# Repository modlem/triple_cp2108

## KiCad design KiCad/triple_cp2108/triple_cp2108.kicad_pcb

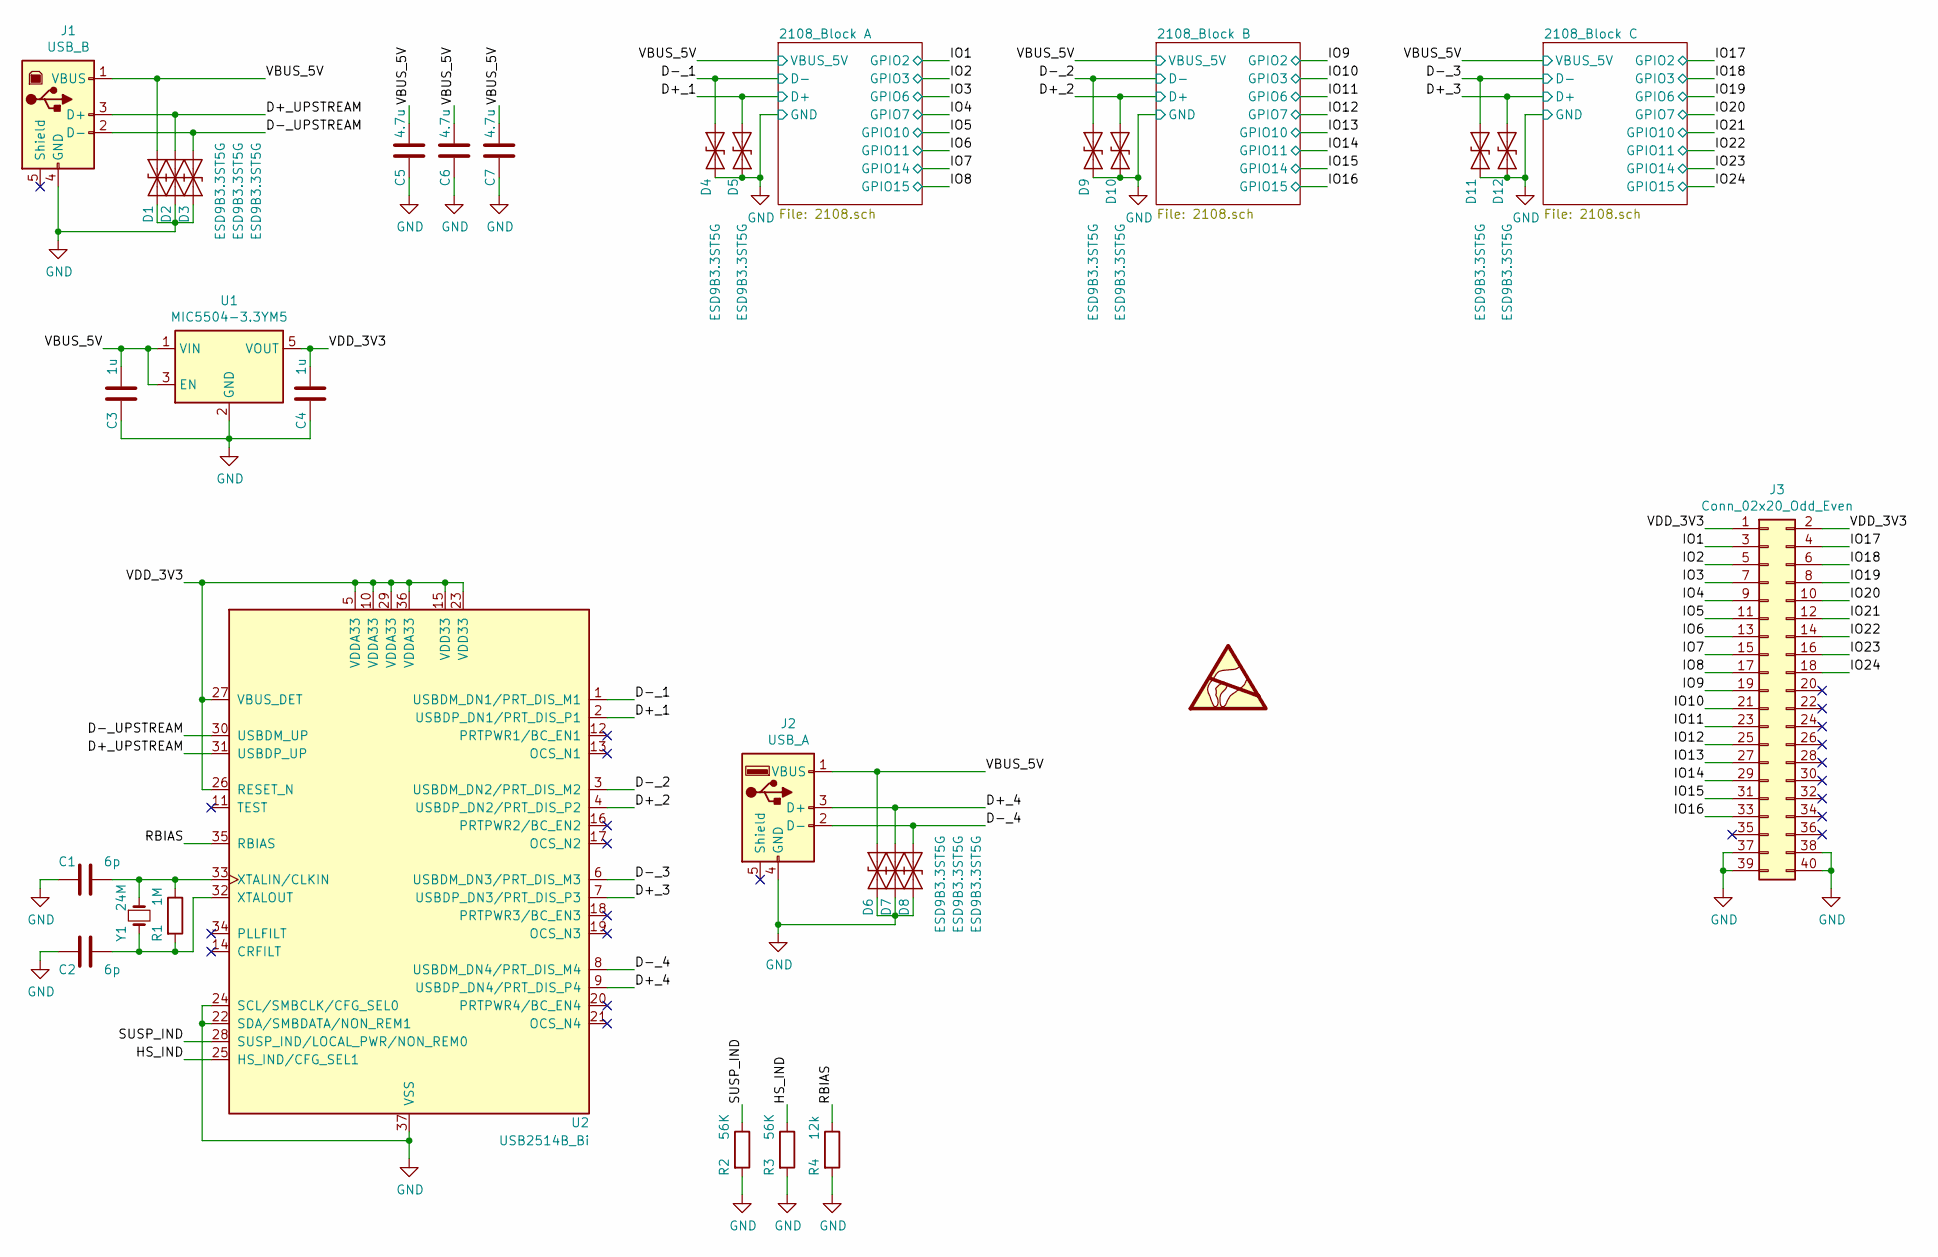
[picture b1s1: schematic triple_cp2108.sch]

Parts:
C1, C2: 6p; C_0805_2012Metric_Pad1.18x1.45mm_HandSolder
C3, C4: 1u; C_0805_2012Metric_Pad1.18x1.45mm_HandSolder
C5, C6, C7: 4.7u; C_0805_2012Metric_Pad1.18x1.45mm_HandSolder
D1, D2, D3, D4, D5, D6, D7, D8, D9, D10, D11, D12: ESD9B3.3ST5G; D_SOD-923
J1: USB_B; USB_B_OST_USB-B1HSxx_Horizontal
J2: USB_A; USB_A_CONNFLY_DS1095-WNR0
J3: Conn_02x20_Odd_Even; PinHeader_2x20_P2.54mm_Vertical
R1: 1M; R_0805_2012Metric_Pad1.20x1.40mm_HandSolder
R2, R3: 56K; R_0805_2012Metric_Pad1.20x1.40mm_HandSolder
R4: 12k; R_0805_2012Metric_Pad1.20x1.40mm_HandSolder
U1: MIC5504-3.3YM5; SOT-23-5
U2: USB2514B_Bi; QFN-36-1EP_6x6mm_P0.5mm_EP3.7x3.7mm
Y1: 24M; Crystal_SMD_2016-4Pin_2.0x1.6mm; Manufacturer_Part_Number XRCGB24M000F2P00R0

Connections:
/D+_1: D5.1 (A1), U2.2 (USBDP_DN1/PRT_DIS_P1); also elsewhere on the board
/D+_2: D10.1 (A1), U2.4 (USBDP_DN2/PRT_DIS_P2); also elsewhere on the board
/D+_3: D12.1 (A1), U2.7 (USBDP_DN3/PRT_DIS_P3); also elsewhere on the board
/D+_4: D7.1 (A1), J2.3 (D+), U2.9 (USBDP_DN4/PRT_DIS_P4)
/D+_UPSTREAM: D2.1 (A1), J1.3 (D+), U2.31 (USBDP_UP)
/D-_1: D4.1 (A1), U2.1 (USBDM_DN1/PRT_DIS_M1); also elsewhere on the board
/D-_2: D9.1 (A1), U2.3 (USBDM_DN2/PRT_DIS_M2); also elsewhere on the board
/D-_3: D11.1 (A1), U2.6 (USBDM_DN3/PRT_DIS_M3); also elsewhere on the board
/D-_4: D8.1 (A1), J2.2 (D-), U2.8 (USBDM_DN4/PRT_DIS_M4)
/D-_UPSTREAM: D3.1 (A1), J1.2 (D-), U2.30 (USBDM_UP)
/HS_IND: R3.1, U2.25 (HS_IND/CFG_SEL1)
/IO1: J3.3; also elsewhere on the board
/IO2: J3.5; also elsewhere on the board
/IO3: J3.7; also elsewhere on the board
/IO4: J3.9; also elsewhere on the board
/IO5: J3.11; also elsewhere on the board
/IO6: J3.13; also elsewhere on the board
/IO7: J3.15; also elsewhere on the board
/IO8: J3.17; also elsewhere on the board
/IO9: J3.19; also elsewhere on the board
/IO10: J3.21; also elsewhere on the board
/IO11: J3.23; also elsewhere on the board
/IO12: J3.25; also elsewhere on the board
/IO13: J3.27; also elsewhere on the board
/IO14: J3.29; also elsewhere on the board
/IO15: J3.31; also elsewhere on the board
/IO16: J3.33; also elsewhere on the board
/IO17: J3.4; also elsewhere on the board
/IO18: J3.6; also elsewhere on the board
/IO19: J3.8; also elsewhere on the board
/IO20: J3.10; also elsewhere on the board
/IO21: J3.12; also elsewhere on the board
/IO22: J3.14; also elsewhere on the board
/IO23: J3.16; also elsewhere on the board
/IO24: J3.18; also elsewhere on the board
/RBIAS: R4.1, U2.35 (RBIAS)
/SUSP_IND: R2.1, U2.28 (SUSP_IND/LOCAL_PWR/NON_REM0)
/VBUS_5V: C3.2, C5.2, C6.2, C7.2, D1.1 (A1), D6.1 (A1), J1.1 (VBUS), J2.1 (VBUS), U1.1 (VIN), U1.3 (EN); also elsewhere on the board
/VDD_3V3: C4.2, J3.1, J3.2, U1.5 (VOUT), U2.5 (VDDA33), U2.10 (VDDA33), U2.15 (VDD33), U2.23 (VDD33), U2.26 (RESET_N), U2.27 (VBUS_DET), U2.29 (VDDA33), U2.36 (VDDA33)
GND: C1.2, C2.2, C3.1, C4.1, C5.1, C6.1, C7.1, D1.2 (A2), D2.2 (A2), D3.2 (A2), D4.2 (A2), D5.2 (A2), D6.2 (A2), D7.2 (A2), D8.2 (A2), D9.2 (A2), D10.2 (A2), D11.2 (A2), D12.2 (A2), J1.4 (GND), J2.4 (GND), J3.37, J3.38, J3.39, J3.40, R2.2, R3.2, R4.2, U1.2 (GND), U2.22 (SDA/SMBDATA/NON_REM1), U2.24 (SCL/SMBCLK/CFG_SEL0), U2.37 (VSS); also elsewhere on the board
unnamed: C1.1, R1.1, U2.33 (XTALIN/CLKIN), Y1.1
unnamed: C2.1, R1.2, U2.32 (XTALOUT), Y1.2

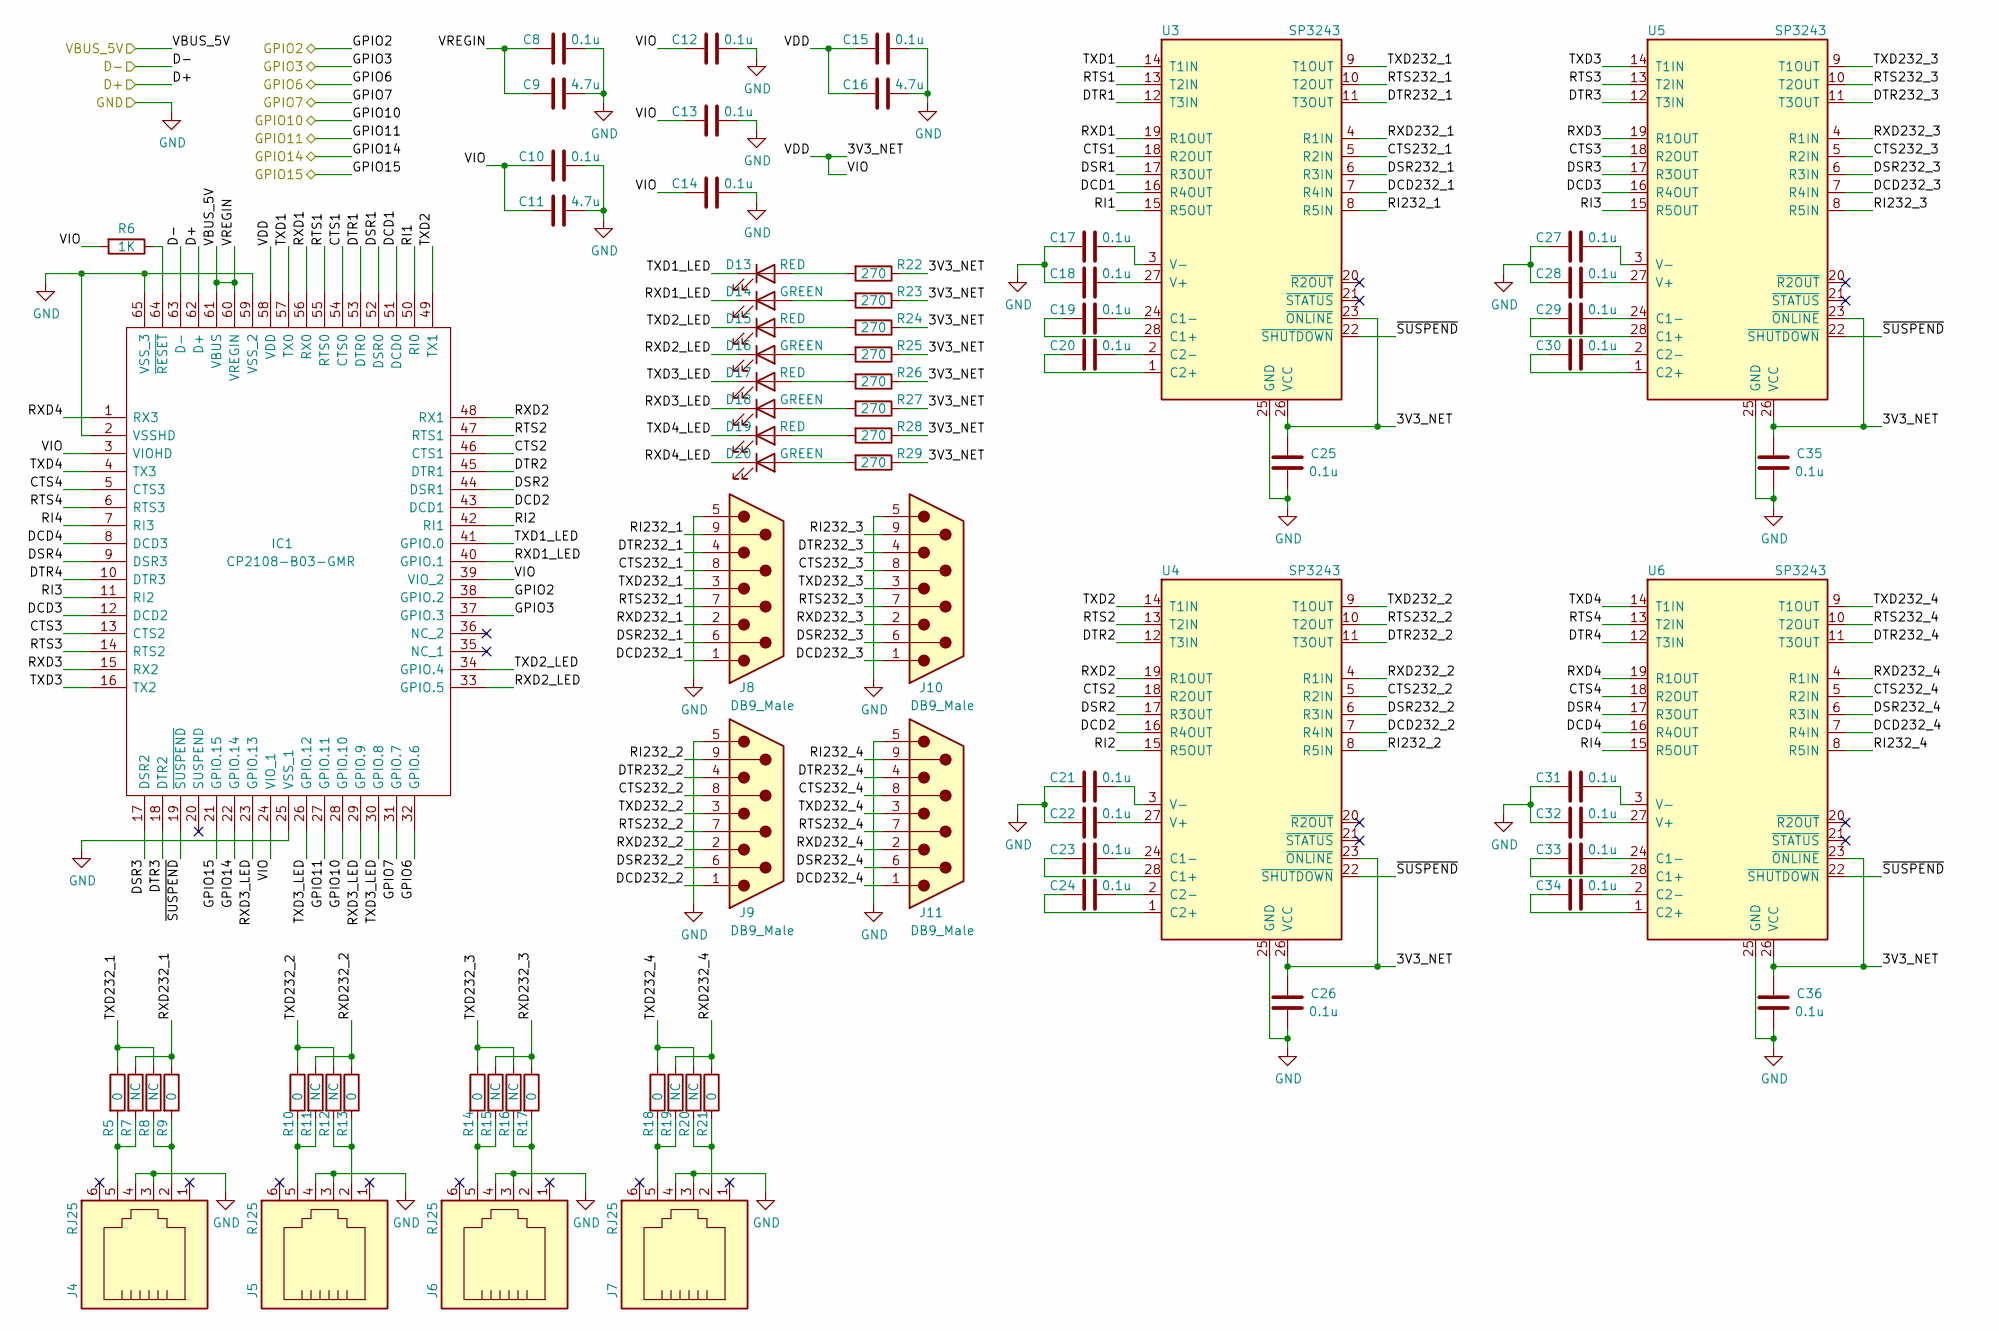
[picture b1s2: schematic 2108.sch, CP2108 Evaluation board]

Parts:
C8, C10, C12, C13, C14, C15, C17, C18, C19, C20, C21, C22, C23, C24, C25, C26, C27, C28, C29, C30, C31, C32, C33, C34, C35, C36: 0.1u; C_0805_2012Metric_Pad1.18x1.45mm_HandSolder; Manufacturer_Part_Number C0805C104M5RACTU
C9, C11, C16: 4.7u; C_0805_2012Metric_Pad1.18x1.45mm_HandSolder
D13, D15, D17, D19: RED; LED_0603_1608Metric; Manufacturer_Part_Number LTST-C193KRKT-5A
D14, D16, D18, D20: GREEN; LED_0603_1608Metric; Manufacturer_Part_Number LTST-C193KGKT-5A
IC1: CP2108-B03-GMR; QFN50P900X900X90-65N-D; Mouser Part Number 634-CP2108-B03-GMR
J4, J5, J6, J7: RJ25; RJ25_Wayconn_MJEA-660X1_Horizontal
J8, J9, J10, J11: DB9_Male; DSUB-9_Male_Vertical_P2.77x2.84mm
R5, R9, R10, R13, R14, R17, R18, R21: 0; R_0805_2012Metric_Pad1.20x1.40mm_HandSolder
R6: 1K; R_0805_2012Metric_Pad1.20x1.40mm_HandSolder
R7, R8, R11, R12, R15, R16, R19, R20: NC; R_0805_2012Metric_Pad1.20x1.40mm_HandSolder
R22, R23, R24, R25, R26, R27, R28, R29: 270; R_0805_2012Metric_Pad1.20x1.40mm_HandSolder
U3, U4, U5, U6: SP3243; SSOP-28_5.3x10.2mm_P0.65mm; Manufacturer_Part_Number SP3243EUEY-L/TR

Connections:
/2108_Block A/3V3_NET: C10.2, C11.2, C12.2, C13.2, C14.2, C15.2, C16.2, C25.2, C26.2, C35.2, C36.2, IC1.3 (VIOHD), IC1.24 (VIO_1), IC1.39 (VIO_2), IC1.58 (VDD), R6.2, R22.1, R23.1, R24.1, R25.1, R26.1, R27.1, R28.1, R29.1, U3.23 (~ONLINE), U3.26 (VCC), U4.23 (~ONLINE), U4.26 (VCC), U5.23 (~ONLINE), U5.26 (VCC), U6.23 (~ONLINE), U6.26 (VCC)
/2108_Block A/CTS1: IC1.54 (CTS0), U3.18 (R2OUT)
/2108_Block A/CTS2: IC1.46 (CTS1), U4.18 (R2OUT)
/2108_Block A/CTS3: IC1.13 (CTS2), U5.18 (R2OUT)
/2108_Block A/CTS4: IC1.5 (CTS3), U6.18 (R2OUT)
/2108_Block A/CTS232_1: J8.8, U3.5 (R2IN)
/2108_Block A/CTS232_2: J9.8, U4.5 (R2IN)
/2108_Block A/CTS232_3: J10.8, U5.5 (R2IN)
/2108_Block A/CTS232_4: J11.8, U6.5 (R2IN)
/2108_Block A/DCD1: IC1.51 (DCD0), U3.16 (R4OUT)
/2108_Block A/DCD2: IC1.43 (DCD1), U4.16 (R4OUT)
/2108_Block A/DCD3: IC1.12 (DCD2), U5.16 (R4OUT)
/2108_Block A/DCD4: IC1.8 (DCD3), U6.16 (R4OUT)
/2108_Block A/DCD232_1: J8.1, U3.7 (R4IN)
/2108_Block A/DCD232_2: J9.1, U4.7 (R4IN)
/2108_Block A/DCD232_3: J10.1, U5.7 (R4IN)
/2108_Block A/DCD232_4: J11.1, U6.7 (R4IN)
/2108_Block A/DSR1: IC1.52 (DSR0), U3.17 (R3OUT)
/2108_Block A/DSR2: IC1.44 (DSR1), U4.17 (R3OUT)
/2108_Block A/DSR3: IC1.17 (DSR2), U5.17 (R3OUT)
/2108_Block A/DSR4: IC1.9 (DSR3), U6.17 (R3OUT)
/2108_Block A/DSR232_1: J8.6, U3.6 (R3IN)
/2108_Block A/DSR232_2: J9.6, U4.6 (R3IN)
/2108_Block A/DSR232_3: J10.6, U5.6 (R3IN)
/2108_Block A/DSR232_4: J11.6, U6.6 (R3IN)
/2108_Block A/DTR1: IC1.53 (DTR0), U3.12 (T3IN)
/2108_Block A/DTR2: IC1.45 (DTR1), U4.12 (T3IN)
/2108_Block A/DTR3: IC1.18 (DTR2), U5.12 (T3IN)
/2108_Block A/DTR4: IC1.10 (DTR3), U6.12 (T3IN)
/2108_Block A/DTR232_1: J8.4, U3.11 (T3OUT)
/2108_Block A/DTR232_2: J9.4, U4.11 (T3OUT)
/2108_Block A/DTR232_3: J10.4, U5.11 (T3OUT)
/2108_Block A/DTR232_4: J11.4, U6.11 (T3OUT)
/2108_Block A/RI1: IC1.50 (RI0), U3.15 (R5OUT)
/2108_Block A/RI2: IC1.42 (RI1), U4.15 (R5OUT)
/2108_Block A/RI3: IC1.11 (RI2), U5.15 (R5OUT)
/2108_Block A/RI4: IC1.7 (RI3), U6.15 (R5OUT)
/2108_Block A/RI232_1: J8.9, U3.8 (R5IN)
/2108_Block A/RI232_2: J9.9, U4.8 (R5IN)
/2108_Block A/RI232_3: J10.9, U5.8 (R5IN)
/2108_Block A/RI232_4: J11.9, U6.8 (R5IN)
/2108_Block A/RTS1: IC1.55 (RTS0), U3.13 (T2IN)
/2108_Block A/RTS2: IC1.47 (RTS1), U4.13 (T2IN)
/2108_Block A/RTS3: IC1.14 (RTS2), U5.13 (T2IN)
/2108_Block A/RTS4: IC1.6 (RTS3), U6.13 (T2IN)
/2108_Block A/RTS232_1: J8.7, U3.10 (T2OUT)
/2108_Block A/RTS232_2: J9.7, U4.10 (T2OUT)
/2108_Block A/RTS232_3: J10.7, U5.10 (T2OUT)
/2108_Block A/RTS232_4: J11.7, U6.10 (T2OUT)
/2108_Block A/RXD1: IC1.56 (RX0), U3.19 (R1OUT)
/2108_Block A/RXD1_LED: D14.1 (K), IC1.40 (GPIO.1)
/2108_Block A/RXD2: IC1.48 (RX1), U4.19 (R1OUT)
/2108_Block A/RXD2_LED: D16.1 (K), IC1.33 (GPIO.5)
/2108_Block A/RXD3: IC1.15 (RX2), U5.19 (R1OUT)
/2108_Block A/RXD4: IC1.1 (RX3), U6.19 (R1OUT)
/2108_Block A/RXD232_1: J8.2, R7.1, R9.1, U3.4 (R1IN)
/2108_Block A/RXD232_2: J9.2, R11.1, R13.1, U4.4 (R1IN)
/2108_Block A/RXD232_3: J10.2, R15.1, R17.1, U5.4 (R1IN)
/2108_Block A/RXD232_4: J11.2, R19.1, R21.1, U6.4 (R1IN)
/2108_Block A/TXD1: IC1.57 (TX0), U3.14 (T1IN)
/2108_Block A/TXD1_LED: D13.1 (K), IC1.41 (GPIO.0)
/2108_Block A/TXD2: IC1.49 (TX1), U4.14 (T1IN)
/2108_Block A/TXD2_LED: D15.1 (K), IC1.34 (GPIO.4)
/2108_Block A/TXD3: IC1.16 (TX2), U5.14 (T1IN)
/2108_Block A/TXD4: IC1.4 (TX3), U6.14 (T1IN)
/2108_Block A/TXD232_1: J8.3, R5.1, R8.1, U3.9 (T1OUT)
/2108_Block A/TXD232_2: J9.3, R10.1, R12.1, U4.9 (T1OUT)
/2108_Block A/TXD232_3: J10.3, R14.1, R16.1, U5.9 (T1OUT)
/2108_Block A/TXD232_4: J11.3, R18.1, R20.1, U6.9 (T1OUT)
/2108_Block A/~SUSPEND: IC1.19 (~SUSPEND), U3.22 (~SHUTDOWN), U4.22 (~SHUTDOWN), U5.22 (~SHUTDOWN), U6.22 (~SHUTDOWN)
/D+_1: IC1.62 (D+); also elsewhere on the board
/D-_1: IC1.63 (D-); also elsewhere on the board
/IO1: IC1.38 (GPIO.2); also elsewhere on the board
/IO2: IC1.37 (GPIO.3); also elsewhere on the board
/IO3: IC1.32 (GPIO.6); also elsewhere on the board
/IO4: IC1.31 (GPIO.7); also elsewhere on the board
/IO5: IC1.28 (GPIO.10); also elsewhere on the board
/IO6: IC1.27 (GPIO.11); also elsewhere on the board
/IO7: IC1.22 (GPIO.14); also elsewhere on the board
/IO8: IC1.21 (GPIO.15); also elsewhere on the board
/VBUS_5V: C8.2, C9.2, IC1.60 (VREGIN), IC1.61 (VBUS); also elsewhere on the board
GND: C8.1, C9.1, C10.1, C11.1, C12.1, C13.1, C14.1, C15.1, C16.1, C17.2, C18.2, C21.2, C22.2, C25.1, C26.1, C27.2, C28.2, C31.2, C32.2, C35.1, C36.1, IC1.2 (VSSHD), IC1.25 (VSS_1), IC1.59 (VSS_2), IC1.65 (VSS_3), J4.3, J4.4, J5.3, J5.4, J6.3, J6.4, J7.3, J7.4, J8.5, J9.5, J10.5, J11.5, U3.25 (GND), U4.25 (GND), U5.25 (GND), U6.25 (GND); also elsewhere on the board
unnamed: C17.1, U3.3 (V-)
unnamed: C18.1, U3.27 (V+)
unnamed: C19.1, U3.24 (C1-)
unnamed: C19.2, U3.28 (C1+)
unnamed: C20.1, U3.2 (C2-)
unnamed: C20.2, U3.1 (C2+)
unnamed: C21.1, U4.3 (V-)
unnamed: C22.1, U4.27 (V+)
unnamed: C23.1, U4.24 (C1-)
unnamed: C23.2, U4.28 (C1+)
unnamed: C24.1, U4.2 (C2-)
unnamed: C24.2, U4.1 (C2+)
unnamed: C27.1, U5.3 (V-)
unnamed: C28.1, U5.27 (V+)
unnamed: C29.1, U5.24 (C1-)
unnamed: C29.2, U5.28 (C1+)
unnamed: C30.1, U5.2 (C2-)
unnamed: C30.2, U5.1 (C2+)
unnamed: C31.1, U6.3 (V-)
unnamed: C32.1, U6.27 (V+)
unnamed: C33.1, U6.24 (C1-)
unnamed: C33.2, U6.28 (C1+)
unnamed: C34.1, U6.2 (C2-)
unnamed: C34.2, U6.1 (C2+)
unnamed: D13.2 (A), R22.2
unnamed: D14.2 (A), R23.2
unnamed: D15.2 (A), R24.2
unnamed: D16.2 (A), R25.2
unnamed: D17.2 (A), R26.2
unnamed: D18.2 (A), R27.2
unnamed: D19.2 (A), R28.2
unnamed: D20.2 (A), R29.2
unnamed: IC1.64 (~RESET), R6.1
unnamed: J4.2, R8.2, R9.2
unnamed: J4.5, R5.2, R7.2
unnamed: J5.2, R12.2, R13.2
unnamed: J5.5, R10.2, R11.2
unnamed: J6.2, R16.2, R17.2
unnamed: J6.5, R14.2, R15.2
unnamed: J7.2, R20.2, R21.2
unnamed: J7.5, R18.2, R19.2

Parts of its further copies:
C37, C39, C41, C42, C43, C44, C46, C47, C48, C49, C50, C51, C52, C53, C54, C55, C56, C57, C58, C59, C60, C61, C62, C63, C64, C65, C66, C68, C70, C71, C72, C73, C75, C76, C77, C78, C79, C80, C81, C82, C83, C84, C85, C86, C87, C88, C89, C90, C91, C92, C93, C94: 0.1u; C_0805_2012Metric_Pad1.18x1.45mm_HandSolder; Manufacturer_Part_Number C0805C104M5RACTU
C38, C40, C45, C67, C69, C74: 4.7u; C_0805_2012Metric_Pad1.18x1.45mm_HandSolder
D21, D23, D25, D27, D29, D31, D33, D35: RED; LED_0603_1608Metric; Manufacturer_Part_Number LTST-C193KRKT-5A
D22, D24, D26, D28, D30, D32, D34, D36: GREEN; LED_0603_1608Metric; Manufacturer_Part_Number LTST-C193KGKT-5A
IC2, IC3: CP2108-B03-GMR; QFN50P900X900X90-65N-D; Mouser Part Number 634-CP2108-B03-GMR
J12, J13, J14, J15, J20, J21, J22, J23: RJ25; RJ25_Wayconn_MJEA-660X1_Horizontal
J16, J17, J18, J19, J24, J25, J26, J27: DB9_Male; DSUB-9_Male_Vertical_P2.77x2.84mm
R30, R34, R35, R38, R39, R42, R43, R46, R55, R59, R60, R63, R64, R67, R68, R71: 0; R_0805_2012Metric_Pad1.20x1.40mm_HandSolder
R31, R56: 1K; R_0805_2012Metric_Pad1.20x1.40mm_HandSolder
R32, R33, R36, R37, R40, R41, R44, R45, R57, R58, R61, R62, R65, R66, R69, R70: NC; R_0805_2012Metric_Pad1.20x1.40mm_HandSolder
R47, R48, R49, R50, R51, R52, R53, R54, R72, R73, R74, R75, R76, R77, R78, R79: 270; R_0805_2012Metric_Pad1.20x1.40mm_HandSolder
U7, U8, U9, U10, U11, U12, U13, U14: SP3243; SSOP-28_5.3x10.2mm_P0.65mm; Manufacturer_Part_Number SP3243EUEY-L/TR

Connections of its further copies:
/2108_Block B/3V3_NET: C39.2, C40.2, C41.2, C42.2, C43.2, C44.2, C45.2, C54.2, C55.2, C64.2, C65.2, IC2.3 (VIOHD), IC2.24 (VIO_1), IC2.39 (VIO_2), IC2.58 (VDD), R31.2, R47.1, R48.1, R49.1, R50.1, R51.1, R52.1, R53.1, R54.1, U7.23 (~ONLINE), U7.26 (VCC), U8.23 (~ONLINE), U8.26 (VCC), U9.23 (~ONLINE), U9.26 (VCC), U10.23 (~ONLINE), U10.26 (VCC)
/2108_Block B/CTS1: IC2.54 (CTS0), U7.18 (R2OUT)
/2108_Block B/CTS2: IC2.46 (CTS1), U8.18 (R2OUT)
/2108_Block B/CTS3: IC2.13 (CTS2), U9.18 (R2OUT)
/2108_Block B/CTS4: IC2.5 (CTS3), U10.18 (R2OUT)
/2108_Block B/CTS232_1: J16.8, U7.5 (R2IN)
/2108_Block B/CTS232_2: J17.8, U8.5 (R2IN)
/2108_Block B/CTS232_3: J18.8, U9.5 (R2IN)
/2108_Block B/CTS232_4: J19.8, U10.5 (R2IN)
/2108_Block B/DCD1: IC2.51 (DCD0), U7.16 (R4OUT)
/2108_Block B/DCD2: IC2.43 (DCD1), U8.16 (R4OUT)
/2108_Block B/DCD3: IC2.12 (DCD2), U9.16 (R4OUT)
/2108_Block B/DCD4: IC2.8 (DCD3), U10.16 (R4OUT)
/2108_Block B/DCD232_1: J16.1, U7.7 (R4IN)
/2108_Block B/DCD232_2: J17.1, U8.7 (R4IN)
/2108_Block B/DCD232_3: J18.1, U9.7 (R4IN)
/2108_Block B/DCD232_4: J19.1, U10.7 (R4IN)
/2108_Block B/DSR1: IC2.52 (DSR0), U7.17 (R3OUT)
/2108_Block B/DSR2: IC2.44 (DSR1), U8.17 (R3OUT)
/2108_Block B/DSR3: IC2.17 (DSR2), U9.17 (R3OUT)
/2108_Block B/DSR4: IC2.9 (DSR3), U10.17 (R3OUT)
/2108_Block B/DSR232_1: J16.6, U7.6 (R3IN)
/2108_Block B/DSR232_2: J17.6, U8.6 (R3IN)
/2108_Block B/DSR232_3: J18.6, U9.6 (R3IN)
/2108_Block B/DSR232_4: J19.6, U10.6 (R3IN)
/2108_Block B/DTR1: IC2.53 (DTR0), U7.12 (T3IN)
/2108_Block B/DTR2: IC2.45 (DTR1), U8.12 (T3IN)
/2108_Block B/DTR3: IC2.18 (DTR2), U9.12 (T3IN)
/2108_Block B/DTR4: IC2.10 (DTR3), U10.12 (T3IN)
/2108_Block B/DTR232_1: J16.4, U7.11 (T3OUT)
/2108_Block B/DTR232_2: J17.4, U8.11 (T3OUT)
/2108_Block B/DTR232_3: J18.4, U9.11 (T3OUT)
/2108_Block B/DTR232_4: J19.4, U10.11 (T3OUT)
/2108_Block B/RI1: IC2.50 (RI0), U7.15 (R5OUT)
/2108_Block B/RI2: IC2.42 (RI1), U8.15 (R5OUT)
/2108_Block B/RI3: IC2.11 (RI2), U9.15 (R5OUT)
/2108_Block B/RI4: IC2.7 (RI3), U10.15 (R5OUT)
/2108_Block B/RI232_1: J16.9, U7.8 (R5IN)
/2108_Block B/RI232_2: J17.9, U8.8 (R5IN)
/2108_Block B/RI232_3: J18.9, U9.8 (R5IN)
/2108_Block B/RI232_4: J19.9, U10.8 (R5IN)
/2108_Block B/RTS1: IC2.55 (RTS0), U7.13 (T2IN)
/2108_Block B/RTS2: IC2.47 (RTS1), U8.13 (T2IN)
/2108_Block B/RTS3: IC2.14 (RTS2), U9.13 (T2IN)
/2108_Block B/RTS4: IC2.6 (RTS3), U10.13 (T2IN)
/2108_Block B/RTS232_1: J16.7, U7.10 (T2OUT)
/2108_Block B/RTS232_2: J17.7, U8.10 (T2OUT)
/2108_Block B/RTS232_3: J18.7, U9.10 (T2OUT)
/2108_Block B/RTS232_4: J19.7, U10.10 (T2OUT)
/2108_Block B/RXD1: IC2.56 (RX0), U7.19 (R1OUT)
/2108_Block B/RXD1_LED: D22.1 (K), IC2.40 (GPIO.1)
/2108_Block B/RXD2: IC2.48 (RX1), U8.19 (R1OUT)
/2108_Block B/RXD2_LED: D24.1 (K), IC2.33 (GPIO.5)
/2108_Block B/RXD3: IC2.15 (RX2), U9.19 (R1OUT)
/2108_Block B/RXD3_LED: D26.1 (K), IC2.29 (GPIO.9)
/2108_Block B/RXD4: IC2.1 (RX3), U10.19 (R1OUT)
/2108_Block B/RXD4_LED: D28.1 (K), IC2.23 (GPIO.13)
/2108_Block B/RXD232_1: J16.2, R32.1, R34.1, U7.4 (R1IN)
/2108_Block B/RXD232_2: J17.2, R36.1, R38.1, U8.4 (R1IN)
/2108_Block B/RXD232_3: J18.2, R40.1, R42.1, U9.4 (R1IN)
/2108_Block B/RXD232_4: J19.2, R44.1, R46.1, U10.4 (R1IN)
/2108_Block B/TXD1: IC2.57 (TX0), U7.14 (T1IN)
/2108_Block B/TXD1_LED: D21.1 (K), IC2.41 (GPIO.0)
/2108_Block B/TXD2: IC2.49 (TX1), U8.14 (T1IN)
/2108_Block B/TXD2_LED: D23.1 (K), IC2.34 (GPIO.4)
/2108_Block B/TXD3: IC2.16 (TX2), U9.14 (T1IN)
/2108_Block B/TXD3_LED: D25.1 (K), IC2.30 (GPIO.8)
/2108_Block B/TXD4: IC2.4 (TX3), U10.14 (T1IN)
/2108_Block B/TXD4_LED: D27.1 (K), IC2.26 (GPIO.12)
/2108_Block B/TXD232_1: J16.3, R30.1, R33.1, U7.9 (T1OUT)
/2108_Block B/TXD232_2: J17.3, R35.1, R37.1, U8.9 (T1OUT)
/2108_Block B/TXD232_3: J18.3, R39.1, R41.1, U9.9 (T1OUT)
/2108_Block B/TXD232_4: J19.3, R43.1, R45.1, U10.9 (T1OUT)
/2108_Block B/~SUSPEND: IC2.19 (~SUSPEND), U7.22 (~SHUTDOWN), U8.22 (~SHUTDOWN), U9.22 (~SHUTDOWN), U10.22 (~SHUTDOWN)
/2108_Block C/3V3_NET: C68.2, C69.2, C70.2, C71.2, C72.2, C73.2, C74.2, C83.2, C84.2, C93.2, C94.2, IC3.3 (VIOHD), IC3.24 (VIO_1), IC3.39 (VIO_2), IC3.58 (VDD), R56.2, R72.1, R73.1, R74.1, R75.1, R76.1, R77.1, R78.1, R79.1, U11.23 (~ONLINE), U11.26 (VCC), U12.23 (~ONLINE), U12.26 (VCC), U13.23 (~ONLINE), U13.26 (VCC), U14.23 (~ONLINE), U14.26 (VCC)
/2108_Block C/CTS1: IC3.54 (CTS0), U11.18 (R2OUT)
/2108_Block C/CTS2: IC3.46 (CTS1), U12.18 (R2OUT)
/2108_Block C/CTS3: IC3.13 (CTS2), U13.18 (R2OUT)
/2108_Block C/CTS4: IC3.5 (CTS3), U14.18 (R2OUT)
/2108_Block C/CTS232_1: J24.8, U11.5 (R2IN)
/2108_Block C/CTS232_2: J25.8, U12.5 (R2IN)
/2108_Block C/CTS232_3: J26.8, U13.5 (R2IN)
/2108_Block C/CTS232_4: J27.8, U14.5 (R2IN)
/2108_Block C/DCD1: IC3.51 (DCD0), U11.16 (R4OUT)
/2108_Block C/DCD2: IC3.43 (DCD1), U12.16 (R4OUT)
/2108_Block C/DCD3: IC3.12 (DCD2), U13.16 (R4OUT)
/2108_Block C/DCD4: IC3.8 (DCD3), U14.16 (R4OUT)
/2108_Block C/DCD232_1: J24.1, U11.7 (R4IN)
/2108_Block C/DCD232_2: J25.1, U12.7 (R4IN)
/2108_Block C/DCD232_3: J26.1, U13.7 (R4IN)
/2108_Block C/DCD232_4: J27.1, U14.7 (R4IN)
/2108_Block C/DSR1: IC3.52 (DSR0), U11.17 (R3OUT)
/2108_Block C/DSR2: IC3.44 (DSR1), U12.17 (R3OUT)
/2108_Block C/DSR3: IC3.17 (DSR2), U13.17 (R3OUT)
/2108_Block C/DSR4: IC3.9 (DSR3), U14.17 (R3OUT)
/2108_Block C/DSR232_1: J24.6, U11.6 (R3IN)
/2108_Block C/DSR232_2: J25.6, U12.6 (R3IN)
/2108_Block C/DSR232_3: J26.6, U13.6 (R3IN)
/2108_Block C/DSR232_4: J27.6, U14.6 (R3IN)
/2108_Block C/DTR1: IC3.53 (DTR0), U11.12 (T3IN)
/2108_Block C/DTR2: IC3.45 (DTR1), U12.12 (T3IN)
/2108_Block C/DTR3: IC3.18 (DTR2), U13.12 (T3IN)
/2108_Block C/DTR4: IC3.10 (DTR3), U14.12 (T3IN)
/2108_Block C/DTR232_1: J24.4, U11.11 (T3OUT)
/2108_Block C/DTR232_2: J25.4, U12.11 (T3OUT)
/2108_Block C/DTR232_3: J26.4, U13.11 (T3OUT)
/2108_Block C/DTR232_4: J27.4, U14.11 (T3OUT)
/2108_Block C/RI1: IC3.50 (RI0), U11.15 (R5OUT)
/2108_Block C/RI2: IC3.42 (RI1), U12.15 (R5OUT)
/2108_Block C/RI3: IC3.11 (RI2), U13.15 (R5OUT)
/2108_Block C/RI4: IC3.7 (RI3), U14.15 (R5OUT)
/2108_Block C/RI232_1: J24.9, U11.8 (R5IN)
/2108_Block C/RI232_2: J25.9, U12.8 (R5IN)
/2108_Block C/RI232_3: J26.9, U13.8 (R5IN)
/2108_Block C/RI232_4: J27.9, U14.8 (R5IN)
/2108_Block C/RTS1: IC3.55 (RTS0), U11.13 (T2IN)
/2108_Block C/RTS2: IC3.47 (RTS1), U12.13 (T2IN)
/2108_Block C/RTS3: IC3.14 (RTS2), U13.13 (T2IN)
/2108_Block C/RTS4: IC3.6 (RTS3), U14.13 (T2IN)
/2108_Block C/RTS232_1: J24.7, U11.10 (T2OUT)
/2108_Block C/RTS232_2: J25.7, U12.10 (T2OUT)
/2108_Block C/RTS232_3: J26.7, U13.10 (T2OUT)
/2108_Block C/RTS232_4: J27.7, U14.10 (T2OUT)
/2108_Block C/RXD1: IC3.56 (RX0), U11.19 (R1OUT)
/2108_Block C/RXD1_LED: D30.1 (K), IC3.40 (GPIO.1)
/2108_Block C/RXD2: IC3.48 (RX1), U12.19 (R1OUT)
/2108_Block C/RXD2_LED: D32.1 (K), IC3.33 (GPIO.5)
/2108_Block C/RXD3: IC3.15 (RX2), U13.19 (R1OUT)
/2108_Block C/RXD3_LED: D34.1 (K), IC3.29 (GPIO.9)
/2108_Block C/RXD4: IC3.1 (RX3), U14.19 (R1OUT)
/2108_Block C/RXD4_LED: D36.1 (K), IC3.23 (GPIO.13)
/2108_Block C/RXD232_1: J24.2, R57.1, R59.1, U11.4 (R1IN)
/2108_Block C/RXD232_2: J25.2, R61.1, R63.1, U12.4 (R1IN)
/2108_Block C/RXD232_3: J26.2, R65.1, R67.1, U13.4 (R1IN)
/2108_Block C/RXD232_4: J27.2, R69.1, R71.1, U14.4 (R1IN)
/2108_Block C/TXD1: IC3.57 (TX0), U11.14 (T1IN)
/2108_Block C/TXD1_LED: D29.1 (K), IC3.41 (GPIO.0)
/2108_Block C/TXD2: IC3.49 (TX1), U12.14 (T1IN)
/2108_Block C/TXD2_LED: D31.1 (K), IC3.34 (GPIO.4)
/2108_Block C/TXD3: IC3.16 (TX2), U13.14 (T1IN)
/2108_Block C/TXD3_LED: D33.1 (K), IC3.30 (GPIO.8)
/2108_Block C/TXD4: IC3.4 (TX3), U14.14 (T1IN)
/2108_Block C/TXD4_LED: D35.1 (K), IC3.26 (GPIO.12)
/2108_Block C/TXD232_1: J24.3, R55.1, R58.1, U11.9 (T1OUT)
/2108_Block C/TXD232_2: J25.3, R60.1, R62.1, U12.9 (T1OUT)
/2108_Block C/TXD232_3: J26.3, R64.1, R66.1, U13.9 (T1OUT)
/2108_Block C/TXD232_4: J27.3, R68.1, R70.1, U14.9 (T1OUT)
/2108_Block C/~SUSPEND: IC3.19 (~SUSPEND), U11.22 (~SHUTDOWN), U12.22 (~SHUTDOWN), U13.22 (~SHUTDOWN), U14.22 (~SHUTDOWN)
/D+_2: IC2.62 (D+); also elsewhere on the board
/D+_3: IC3.62 (D+); also elsewhere on the board
/D-_2: IC2.63 (D-); also elsewhere on the board
/D-_3: IC3.63 (D-); also elsewhere on the board
/IO9: IC2.38 (GPIO.2); also elsewhere on the board
/IO10: IC2.37 (GPIO.3); also elsewhere on the board
/IO11: IC2.32 (GPIO.6); also elsewhere on the board
/IO12: IC2.31 (GPIO.7); also elsewhere on the board
/IO13: IC2.28 (GPIO.10); also elsewhere on the board
/IO14: IC2.27 (GPIO.11); also elsewhere on the board
/IO15: IC2.22 (GPIO.14); also elsewhere on the board
/IO16: IC2.21 (GPIO.15); also elsewhere on the board
/IO17: IC3.38 (GPIO.2); also elsewhere on the board
/IO18: IC3.37 (GPIO.3); also elsewhere on the board
/IO19: IC3.32 (GPIO.6); also elsewhere on the board
/IO20: IC3.31 (GPIO.7); also elsewhere on the board
/IO21: IC3.28 (GPIO.10); also elsewhere on the board
/IO22: IC3.27 (GPIO.11); also elsewhere on the board
/IO23: IC3.22 (GPIO.14); also elsewhere on the board
/IO24: IC3.21 (GPIO.15); also elsewhere on the board
/VBUS_5V: C37.2, C38.2, C66.2, C67.2, IC2.60 (VREGIN), IC2.61 (VBUS), IC3.60 (VREGIN), IC3.61 (VBUS); also elsewhere on the board
GND: C37.1, C38.1, C39.1, C40.1, C41.1, C42.1, C43.1, C44.1, C45.1, C46.2, C47.2, C50.2, C51.2, C54.1, C55.1, C56.2, C57.2, C60.2, C61.2, C64.1, C65.1, C66.1, C67.1, C68.1, C69.1, C70.1, C71.1, C72.1, C73.1, C74.1, C75.2, C76.2, C79.2, C80.2, C83.1, C84.1, C85.2, C86.2, C89.2, C90.2, C93.1, C94.1, IC2.2 (VSSHD), IC2.25 (VSS_1), IC2.59 (VSS_2), IC2.65 (VSS_3), IC3.2 (VSSHD), IC3.25 (VSS_1), IC3.59 (VSS_2), IC3.65 (VSS_3), J12.3, J12.4, J13.3, J13.4, J14.3, J14.4, J15.3, J15.4, J16.5, J17.5, J18.5, J19.5, J20.3, J20.4, J21.3, J21.4, J22.3, J22.4, J23.3, J23.4, J24.5, J25.5, J26.5, J27.5, U7.25 (GND), U8.25 (GND), U9.25 (GND), U10.25 (GND), U11.25 (GND), U12.25 (GND), U13.25 (GND), U14.25 (GND); also elsewhere on the board
unnamed: C46.1, U7.3 (V-)
unnamed: C47.1, U7.27 (V+)
unnamed: C48.1, U7.24 (C1-)
unnamed: C48.2, U7.28 (C1+)
unnamed: C49.1, U7.2 (C2-)
unnamed: C49.2, U7.1 (C2+)
unnamed: C50.1, U8.3 (V-)
unnamed: C51.1, U8.27 (V+)
unnamed: C52.1, U8.24 (C1-)
unnamed: C52.2, U8.28 (C1+)
unnamed: C53.1, U8.2 (C2-)
unnamed: C53.2, U8.1 (C2+)
unnamed: C56.1, U9.3 (V-)
unnamed: C57.1, U9.27 (V+)
unnamed: C58.1, U9.24 (C1-)
unnamed: C58.2, U9.28 (C1+)
unnamed: C59.1, U9.2 (C2-)
unnamed: C59.2, U9.1 (C2+)
unnamed: C60.1, U10.3 (V-)
unnamed: C61.1, U10.27 (V+)
unnamed: C62.1, U10.24 (C1-)
unnamed: C62.2, U10.28 (C1+)
unnamed: C63.1, U10.2 (C2-)
unnamed: C63.2, U10.1 (C2+)
unnamed: C75.1, U11.3 (V-)
unnamed: C76.1, U11.27 (V+)
unnamed: C77.1, U11.24 (C1-)
unnamed: C77.2, U11.28 (C1+)
unnamed: C78.1, U11.2 (C2-)
unnamed: C78.2, U11.1 (C2+)
unnamed: C79.1, U12.3 (V-)
unnamed: C80.1, U12.27 (V+)
unnamed: C81.1, U12.24 (C1-)
unnamed: C81.2, U12.28 (C1+)
unnamed: C82.1, U12.2 (C2-)
unnamed: C82.2, U12.1 (C2+)
unnamed: C85.1, U13.3 (V-)
unnamed: C86.1, U13.27 (V+)
unnamed: C87.1, U13.24 (C1-)
unnamed: C87.2, U13.28 (C1+)
unnamed: C88.1, U13.2 (C2-)
unnamed: C88.2, U13.1 (C2+)
unnamed: C89.1, U14.3 (V-)
unnamed: C90.1, U14.27 (V+)
unnamed: C91.1, U14.24 (C1-)
unnamed: C91.2, U14.28 (C1+)
unnamed: C92.1, U14.2 (C2-)
unnamed: C92.2, U14.1 (C2+)
unnamed: D21.2 (A), R47.2
unnamed: D22.2 (A), R48.2
unnamed: D23.2 (A), R49.2
unnamed: D24.2 (A), R50.2
unnamed: D25.2 (A), R51.2
unnamed: D26.2 (A), R52.2
unnamed: D27.2 (A), R53.2
unnamed: D28.2 (A), R54.2
unnamed: D29.2 (A), R72.2
unnamed: D30.2 (A), R73.2
unnamed: D31.2 (A), R74.2
unnamed: D32.2 (A), R75.2
unnamed: D33.2 (A), R76.2
unnamed: D34.2 (A), R77.2
unnamed: D35.2 (A), R78.2
unnamed: D36.2 (A), R79.2
unnamed: IC2.64 (~RESET), R31.1
unnamed: IC3.64 (~RESET), R56.1
unnamed: J12.2, R33.2, R34.2
unnamed: J12.5, R30.2, R32.2
unnamed: J13.2, R37.2, R38.2
unnamed: J13.5, R35.2, R36.2
unnamed: J14.2, R41.2, R42.2
unnamed: J14.5, R39.2, R40.2
unnamed: J15.2, R45.2, R46.2
unnamed: J15.5, R43.2, R44.2
unnamed: J20.2, R58.2, R59.2
unnamed: J20.5, R55.2, R57.2
unnamed: J21.2, R62.2, R63.2
unnamed: J21.5, R60.2, R61.2
unnamed: J22.2, R66.2, R67.2
unnamed: J22.5, R64.2, R65.2
unnamed: J23.2, R70.2, R71.2
unnamed: J23.5, R68.2, R69.2

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
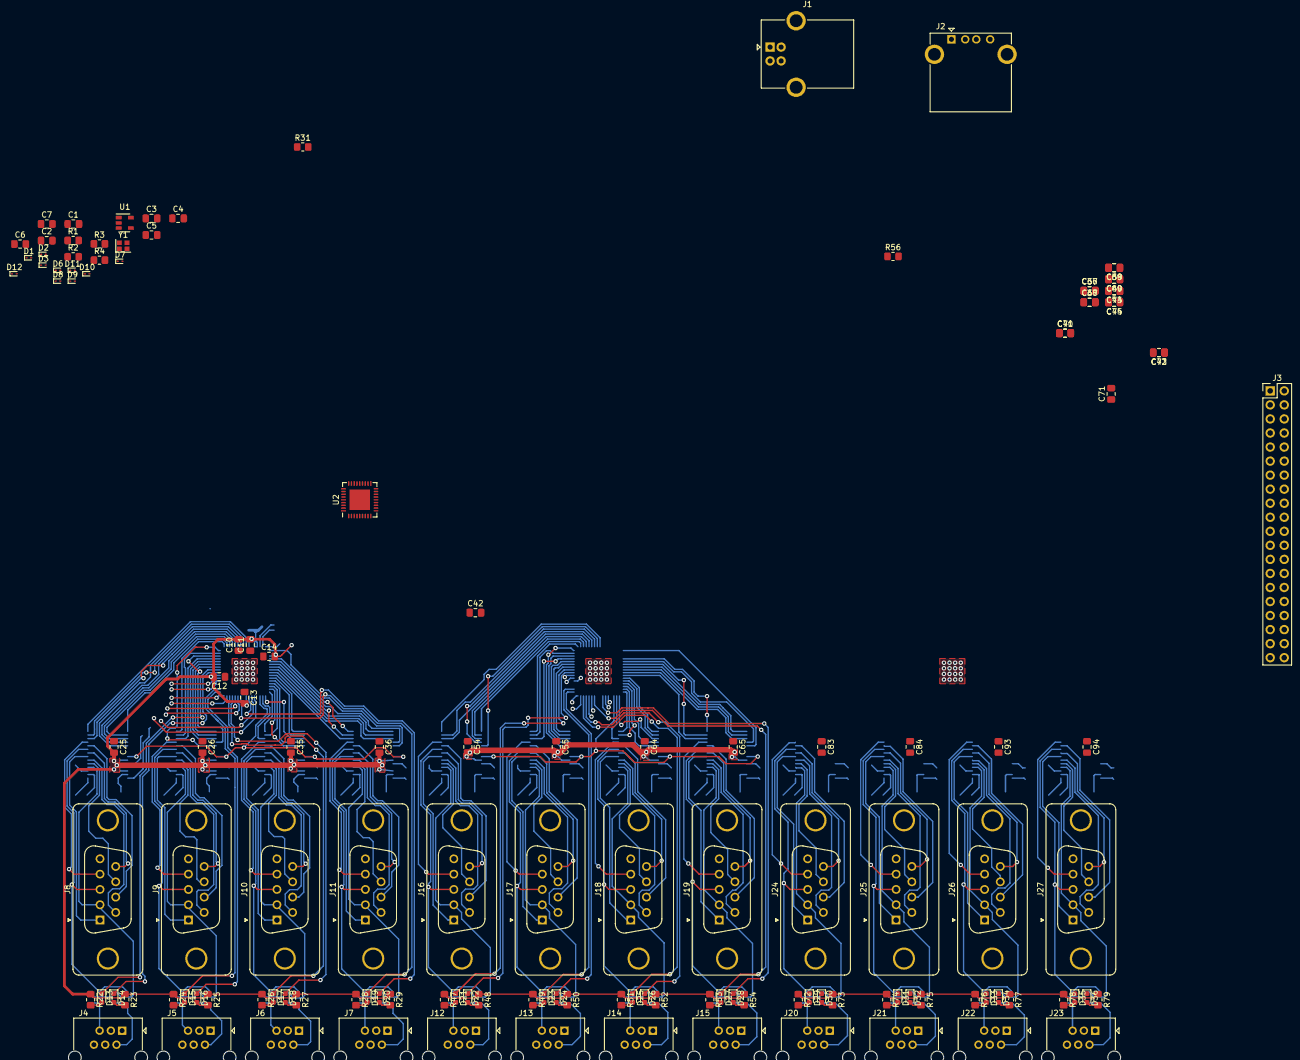
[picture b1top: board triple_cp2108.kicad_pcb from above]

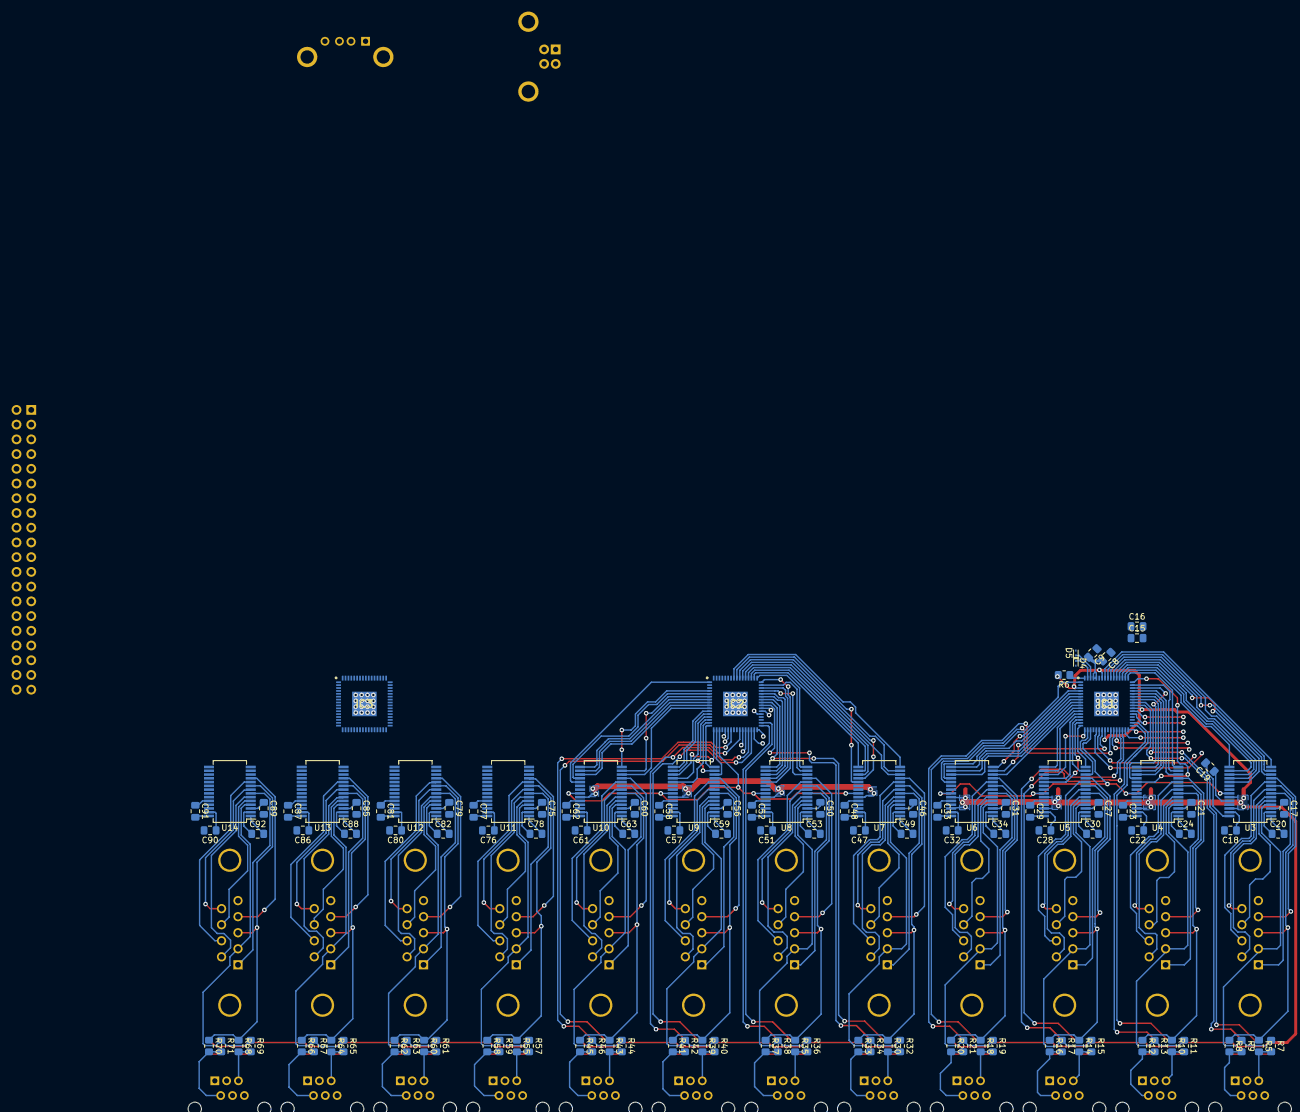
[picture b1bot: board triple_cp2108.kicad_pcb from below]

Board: 2 copper layers, 254 parts (118 on the bottom side), 387 nets.

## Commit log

2020-12-25 Schematic basics
2020-12-25 USB hub stuff
    Microchip USB2514
    - 4 port 2.0 hi-speed hub added
2020-12-25 Parts importing in prgs.
2020-12-25 2108 in prgs.
2020-12-26 2108 done
2020-12-26 GPIO Consolidation in prgs.
2020-12-28 misc.
2020-12-31 Diodes changed
    USB ESD protection diodes changed to individual ones
2021-01-02 BOM consolidation 1
2021-01-02 Netlist generated
2021-01-03 LED resis val changed
2021-01-05 Netlist #2
2021-01-08 Layout in prgs. 1
2021-01-09 Layout in prgs. 2
2021-01-13 layout in prgs
2021-01-23 PCB layout in prgs.
2021-01-23 brd l
2021-01-24 layout revert
2021-05-22 in prgs.
2021-09-21 24v added
    24v ext pow added
    - in prgs.
